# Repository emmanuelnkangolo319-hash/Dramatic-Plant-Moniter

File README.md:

# Dramatic-Plant-Moniter
A plant monitor that makes weird sounds and faces to show when you need to water your plant.

Im making this product so people can connect to their plants abit more, i think replacing the job removes the whole point of getting your own plant. It makes weird sounds and shows how it feels because i wanted it to bring the emotions of the plant to life.

The Electronics:

The CAD:

-The Onshape link:
https://cad.onshape.com/documents/fa7c49e9b4da2c6559626692/w/87dc8cc142b4987819eabf60/e/572d0358d2ebd27b84209106?renderMode=0&uiState=6b05f7f429efc7e069ffbdb8

-V.1

-V.2

I made these changes mainly based on aesthetics. 

The build is fairly simple, all you need to do is replicate the assembly, using double sided tape/glue to sick everything together. i will be realesing a video soon.

My plan is to make this a real product soon. Im making this to push Solarpunk into actual markets, to give people the chance to buy the future they want.

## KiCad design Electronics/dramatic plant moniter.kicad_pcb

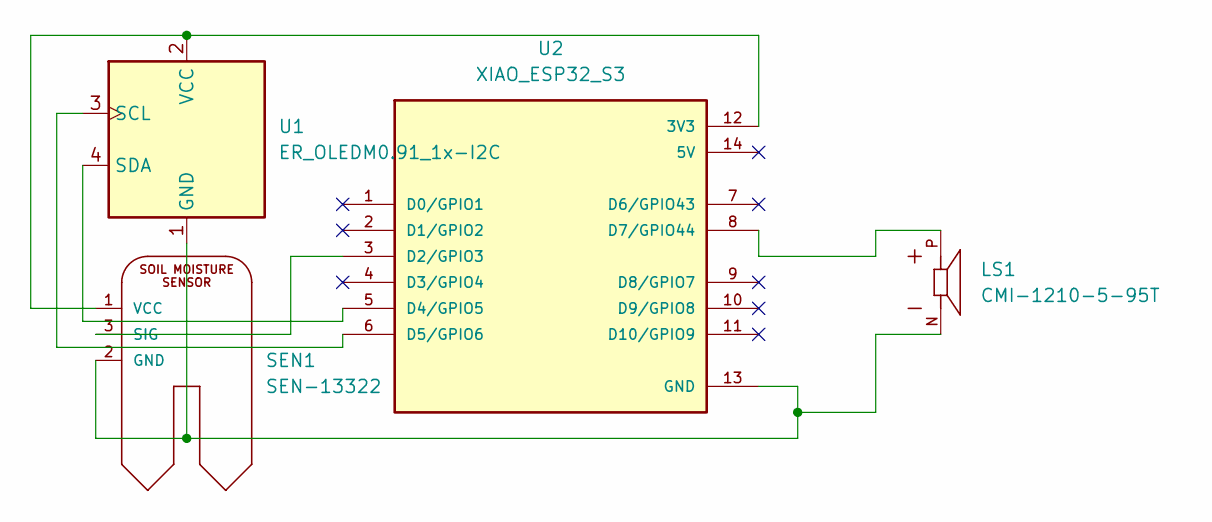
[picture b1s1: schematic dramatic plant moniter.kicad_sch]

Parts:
LS1: CMI-1210-5-95T; XDCR_CMI-1210-5-95T; MPN CMI-1210-5-95T
SEN1: SEN-13322; MPN SEN-13322
U1: ER_OLEDM0.91_1x-I2C
U2: XIAO_ESP32_S3; MODULE_XIAO_ESP32_S3; MPN XIAO ESP32 S3

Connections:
unnamed: LS1.N, SEN1.2 (GND), U1.1 (GND), U2.13 (GND)
unnamed: SEN1.3 (SIG), U2.3 (D2/GPIO3)
unnamed: SEN1.1 (VCC), U1.2 (VCC), U2.12 (3V3)
unnamed: U1.3 (SCL), U2.6 (D5/GPIO6)
unnamed: U1.4 (SDA), U2.5 (D4/GPIO5)
unnamed: LS1.P, U2.8 (D7/GPIO44)

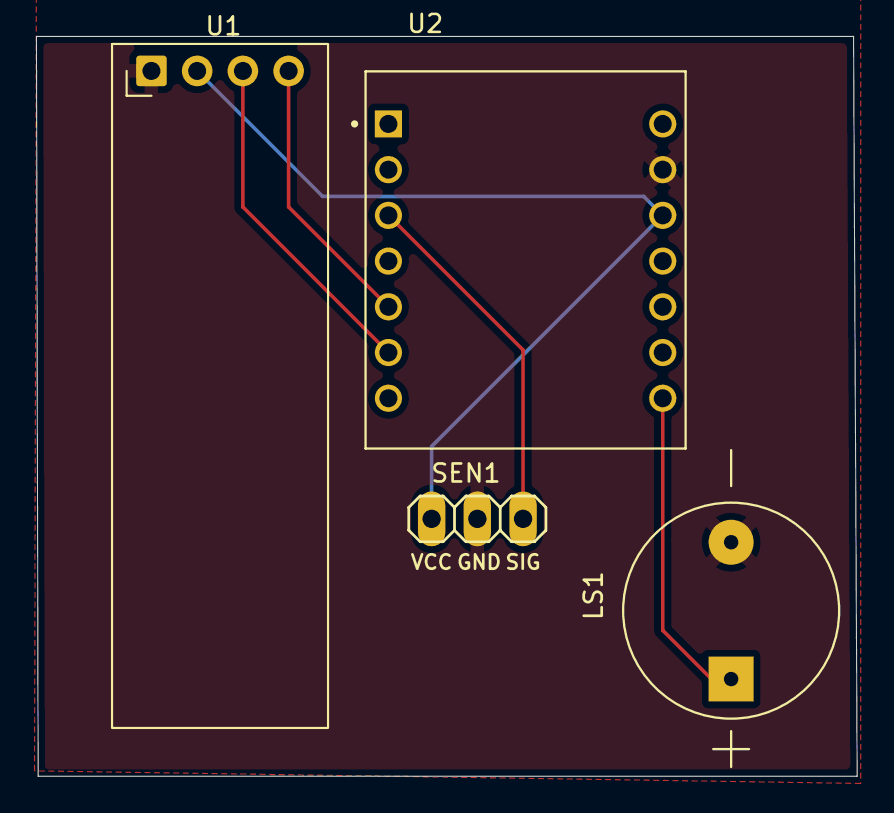
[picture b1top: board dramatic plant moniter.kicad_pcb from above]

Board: 2 copper layers, 45.6 x 41.1 mm, 4 parts (0 on the bottom side), 6 nets.
